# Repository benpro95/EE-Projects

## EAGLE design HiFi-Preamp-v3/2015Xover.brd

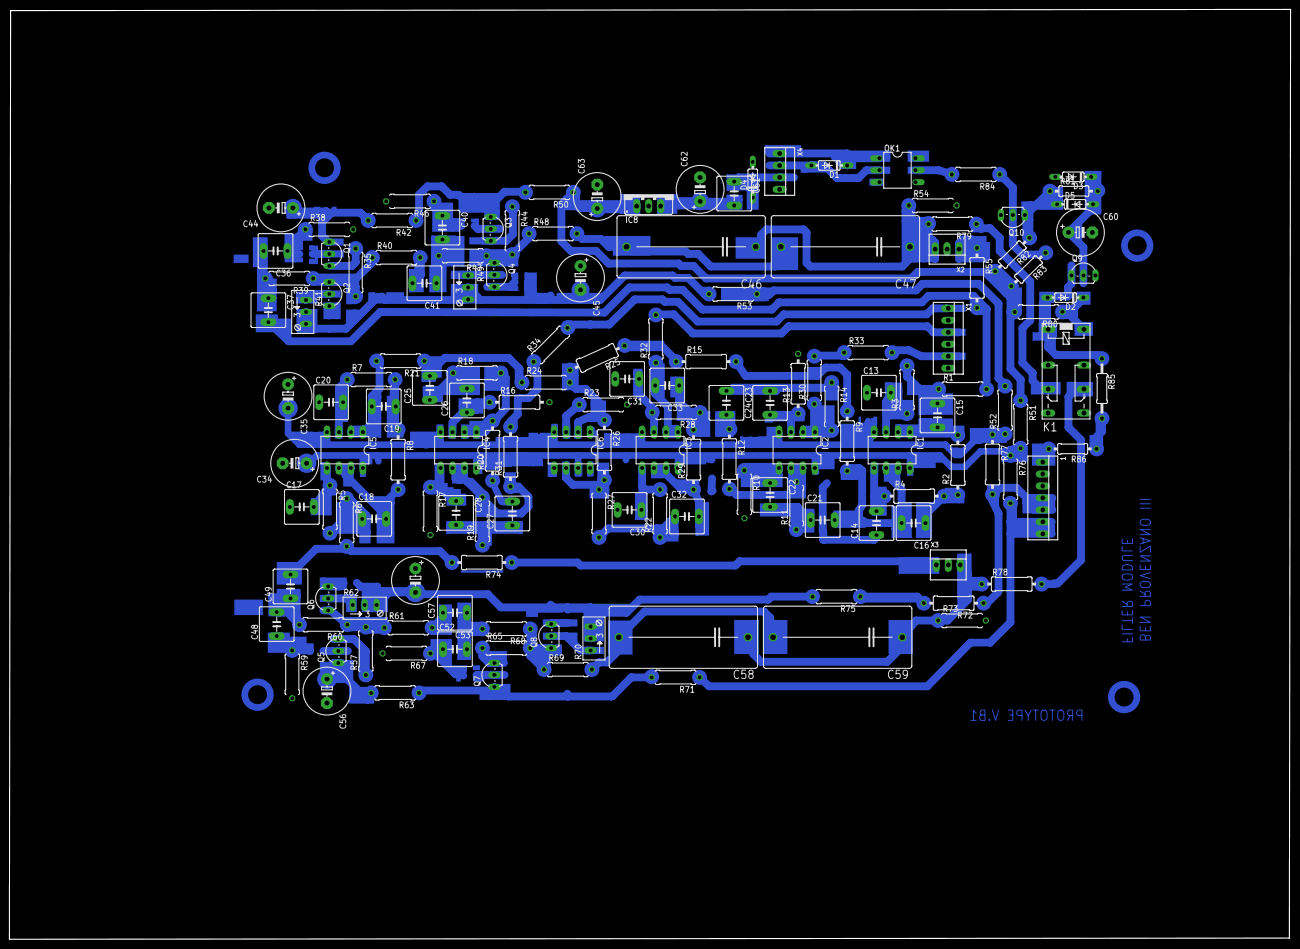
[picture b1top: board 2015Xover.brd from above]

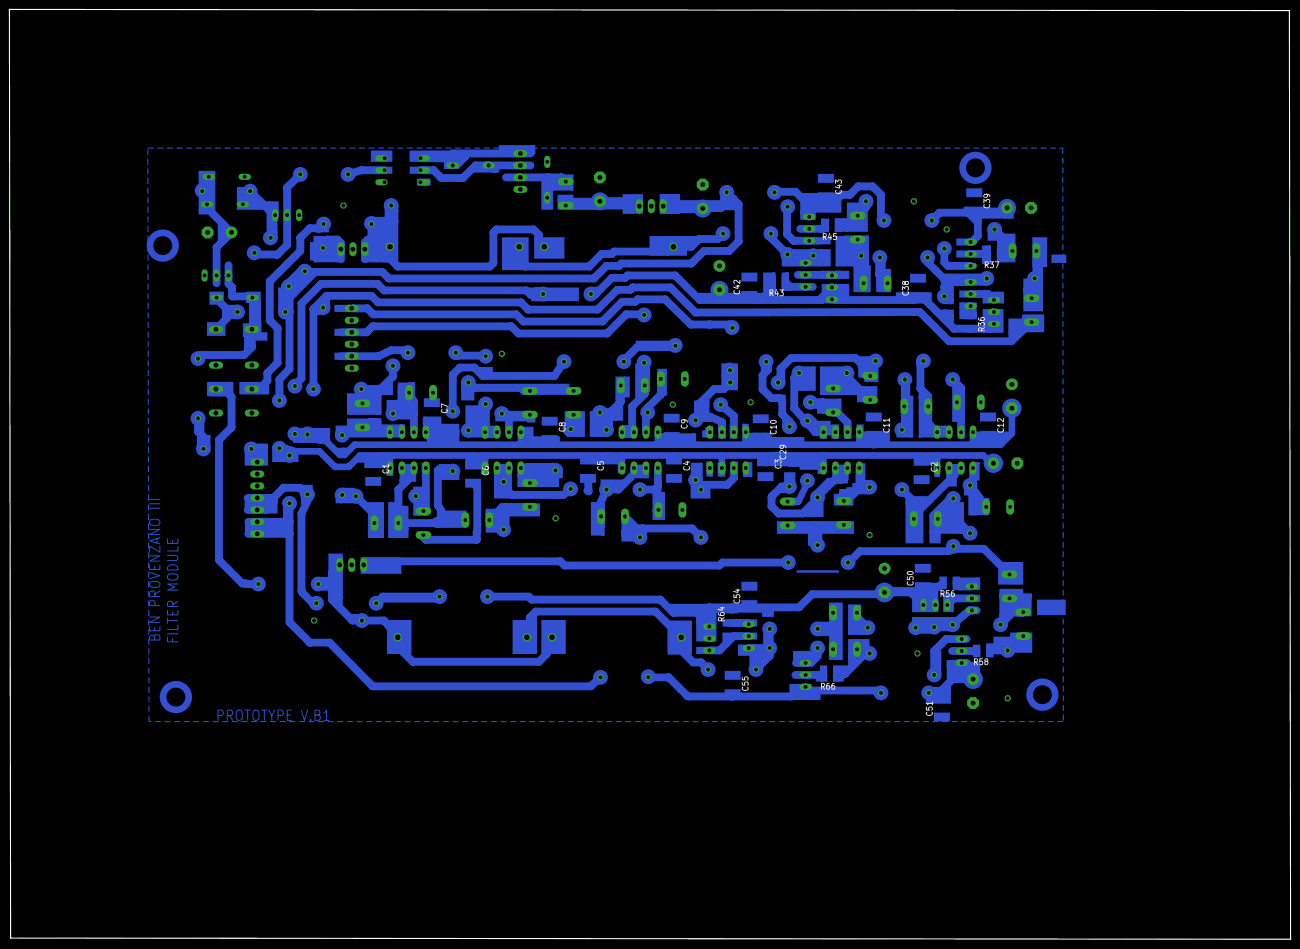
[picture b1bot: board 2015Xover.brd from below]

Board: 2 copper layers, 272.1 x 197.5 mm, 178 parts (29 on the bottom side), 109 nets.

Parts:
1: PWR; 22-23-2071
C1, C2, C3, C4, C5, C6, C7, C8, C9, C10, C11, C12, C29, C38, C39, C42, C43, C50, C51, C54, C55: .1; C4532
C13, C14, C17, C20, C36, C37, C40, C41, C48, C49, C52, C53: 33nF; C050-075X075
C15, C16, C18, C19: 2x33nF; C050-075X075
C21, C22, C23, C24, C25, C26, C27, C28, C30, C31: 100nF; C050-075X075
C32, C33: 2x100nF; C050-075X075
C34, C35, C44, C45, C56, C57, C60, C62: 100uF; E5-10,5
C46, C58: 3u3; C275-134X316
C47, C59: 1uF; C275-134X316
C61: .5APTC; C050-075X075
C63: 47uF; E5-10,5
D1, D5: 4148; DO35-7
D2: 4007; DO35-7
D3: 15v; DO35-7
D4: 15V; DO35-7
IC1, IC2, IC3, IC4, IC5: OPA2134P; DIL08
IC6: OPA134S; DIL08
IC8: 78XXS
K1: 351
OK1: 4N28; DIL06
Q1, Q3, Q5, Q7: K170; TO92-EBC
Q2, Q4, Q6, Q8: J112; TO92-EBC
Q9: 2106; TO92-EBC
Q10: BC546; TO92-EBC
R1: 15K; 0309/10
R2, R4, R8: 15k; 0309/12
R3, R5, R6, R7, R39, R47, R60, R68: 15k; 0309/10
R9, R12, R15, R20, R72, R78: 0; 0309/12
R10, R17: 50K; 0309/10
R11, R14, R18, R19, R22, R27, R28: 25K; 0309/10
R13, R16: 50K; 0309/12
R21, R42, R51, R52, R63, R79, R84: 0; 0309/10
R23: 1K; 0309/10
R24: 10K; 0309/10
R25, R26: 10K; 0309/12
R29: 25K; 0309/12
R30, R32, R40, R48, R61, R69: 118; 0309/10
R31: 118; 0309/12
R33, R34: NA; 0309/10
R35, R44, R50, R53, R57, R65, R71, R75: 5R1; 0309/10
R36, R37, R43, R45, R56, R58, R64, R66: 1K1; R1210
R38, R46, R59, R67: 30K; 0309/10
R41, R49, R62, R70: RJ9W
R54, R73: 100K; 0309/10
R55, R74: NA; 0309/12
R76: 0V+; 0309/10
R77: 0V-; 0309/12
R80: 220; 0309/10
R81: 2M2; 0207/10
R82, R83: 10K; 0207/10
R85: 0; 0207/12
R86: 0; 0207/10
X1: LPF; 22-23-2061
X2, X3: IO; 22-23-2031
X4: KK; 22-23-2041

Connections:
+15V: C1.1, C2.1, C3.1, C4.1, C5.1, C6.1, C29.1, C34.+, IC1.8, IC2.8, IC3.8, IC4.8, IC5.8, IC6.7, R51.2, R76.1
-15V: C7.2, C8.2, C9.2, C10.2, C11.2, C12.2, C29.2, C35.-, IC1.4, IC2.4, IC3.4, IC4.4, IC5.4, IC6.4, R52.1, R77.1
GND: 1.2, 1.3, C1.2, C2.2, C3.2, C4.2, C5.2, C6.2, C7.1, C8.1, C9.1, C10.1, C11.1, C12.1, C13.1, C14.1, C17.1, C20.1, C30.2, C31.2, C34.-, C35.+, C38.2, C39.1, C42.2, C43.1, C44.-, C45.+, C50.2, C51.1, C54.2, C55.1, C56.-, C57.+, C60.-, C62.-, C63.-, D3.A, D4.A, IC8.GND, K1.P1, K1.P2, K1.S1, K1.S2, OK1.4, Q9.E, Q10.E, R10.2, R13.2, R16.2, R17.2, R23.2, R38.2, R46.2, R54.2, R59.2, R67.2, R73.2, X1.2, X1.4, X1.6, X2.2, X3.2, X4.4
unnamed: C15.2, IC1.1, IC1.2, R2.2
unnamed: C23.1, C24.2, R14.1
unnamed: IC2.1, IC2.2, R14.2, R30.1
unnamed: IC2.6, IC2.7, R11.2, R12.2
unnamed: C33.2, IC3.1, IC3.2, R32.1
unnamed: C32.2, IC3.6, IC3.7, R29.1
unnamed: Q2.E, R36.1
unnamed: IC4.6, IC4.7, R19.2, R31.1
unnamed: C18.2, IC5.6, IC5.7, R8.2
unnamed: C19.2, IC5.1, IC5.2, R21.2
unnamed: C16.1, R2.1, R4.2
unnamed: C15.1, R1.1, R3.2
unnamed: C13.2, IC1.3, R3.1
unnamed: C14.2, IC1.5, R4.1
unnamed: C18.1, R5.2, R6.1
unnamed: C17.2, IC5.5, R5.1
unnamed: C20.2, IC5.3, R7.1
unnamed: C19.1, R7.2, R8.1
unnamed: C21.1, C22.2, R11.1
unnamed: C22.1, IC2.5, R10.1
unnamed: C16.2, C21.2, IC1.6, IC1.7, R9.2
unnamed: C24.1, IC2.3, R13.1
unnamed: C23.2, R12.1
unnamed: R9.1, R15.2
unnamed: C27.2, R20.1
unnamed: C27.1, C28.2, R19.1
unnamed: C28.1, IC4.5, R17.1
unnamed: C26.1, IC4.3, R16.1
unnamed: C25.1, C26.2, R18.1
unnamed: R30.2, R33.1
unnamed: R31.2, R34.1
unnamed: Q2.C, R35.2, R39.1, R40.1
unnamed: IC4.1, IC4.2, R18.2, R20.2
unnamed: Q1.E, R35.1
unnamed: C49.2, R6.2, R74.2
unnamed: C39.2, C44.+, Q1.C, R42.2
unnamed: IC6.2, R24.2, R25.2, R26.1
unnamed: IC6.6, R26.2, R27.1
unnamed: C25.2, R21.1, R24.1
unnamed: R15.1, R25.1
unnamed: Q1.B, R37.2
unnamed: C31.1, IC3.3, R28.2
unnamed: C30.1, IC3.5, R22.2
unnamed: C32.1, R22.1, R27.2
unnamed: C33.1, R28.1, R29.2
unnamed: Q2.B, R41.E
unnamed: C36.1, R37.1, R38.1
unnamed: R34.2, X1.1
unnamed: R32.2, X1.3
unnamed: R33.2, X1.5
unnamed: C36.2, C37.1, R39.2
unnamed: C37.2, R1.2, R55.2
unnamed: C41.2, R40.2
unnamed: IC6.3, R23.1
unnamed: C38.1, C42.1, C45.-, R36.2, R41.A, R41.S, R43.2, R49.A, R49.S, R53.2
unnamed: Q4.E, R43.1
unnamed: Q4.C, R44.2, R47.1, R48.1
unnamed: Q3.E, R44.1
unnamed: C43.2, Q3.C, R42.1, R50.2
unnamed: Q3.B, R45.2
unnamed: Q4.B, R49.E
unnamed: C40.1, R45.1, R46.1
unnamed: C40.2, C41.1, R47.2
unnamed: R52.2, R53.1
unnamed: OK1.5, R84.2
unnamed: C46.2, C47.2, R48.2
unnamed: C46.1, C47.1, R54.1, R79.2, X2.3
unnamed: R55.1, X2.1
unnamed: 1.6, 1.7, R71.1, R76.2
unnamed: Q6.E, R56.1
unnamed: Q6.C, R57.2, R60.1, R61.1
unnamed: Q5.E, R57.1
unnamed: C51.2, C56.+, Q5.C, R63.2
unnamed: Q5.B, R58.2
unnamed: Q6.B, R62.E
unnamed: C48.1, R58.1, R59.1
unnamed: C48.2, C49.1, R60.2
unnamed: C50.1, C54.1, C57.-, R56.2, R62.A, R62.S, R64.2, R70.A, R70.S, R75.2
unnamed: C53.2, R61.2
unnamed: Q8.E, R64.1
unnamed: Q8.C, R65.2, R68.1, R69.1
unnamed: Q7.E, R65.1
unnamed: C55.2, Q7.C, R63.1, R71.2
unnamed: Q7.B, R66.2
unnamed: Q8.B, R70.E
unnamed: C52.1, R66.1, R67.1
unnamed: C52.2, C53.1, R68.2
unnamed: D1.C, OK1.1, X4.1
unnamed: R72.2, R75.1
unnamed: C58.2, C59.2, R69.2
unnamed: C58.1, C59.1, R73.1, R78.1, X3.3
unnamed: R74.1, X3.1
unnamed: 1.4, 1.5, R72.1, R77.2
unnamed: D1.A, OK1.2, X4.2
unnamed: K1.O1, R79.1
unnamed: D2.C, K1.16, R80.1
unnamed: C60.+, D3.C, D5.A, Q9.B, R81.2
unnamed: K1.O2, R78.2
unnamed: D2.A, K1.1, Q9.C, R85.1
unnamed: C61.1, D4.C, X4.3
unnamed: C61.2, C62.+, IC8.OUT
unnamed: D5.C, Q10.C, R81.1, R82.1
unnamed: Q10.B, R83.1, R84.1
unnamed: C63.+, IC8.IN, R50.1, R51.1, R80.2, R82.2, R83.2
unnamed: R85.2, R86.1
unnamed: 1.1, R86.2

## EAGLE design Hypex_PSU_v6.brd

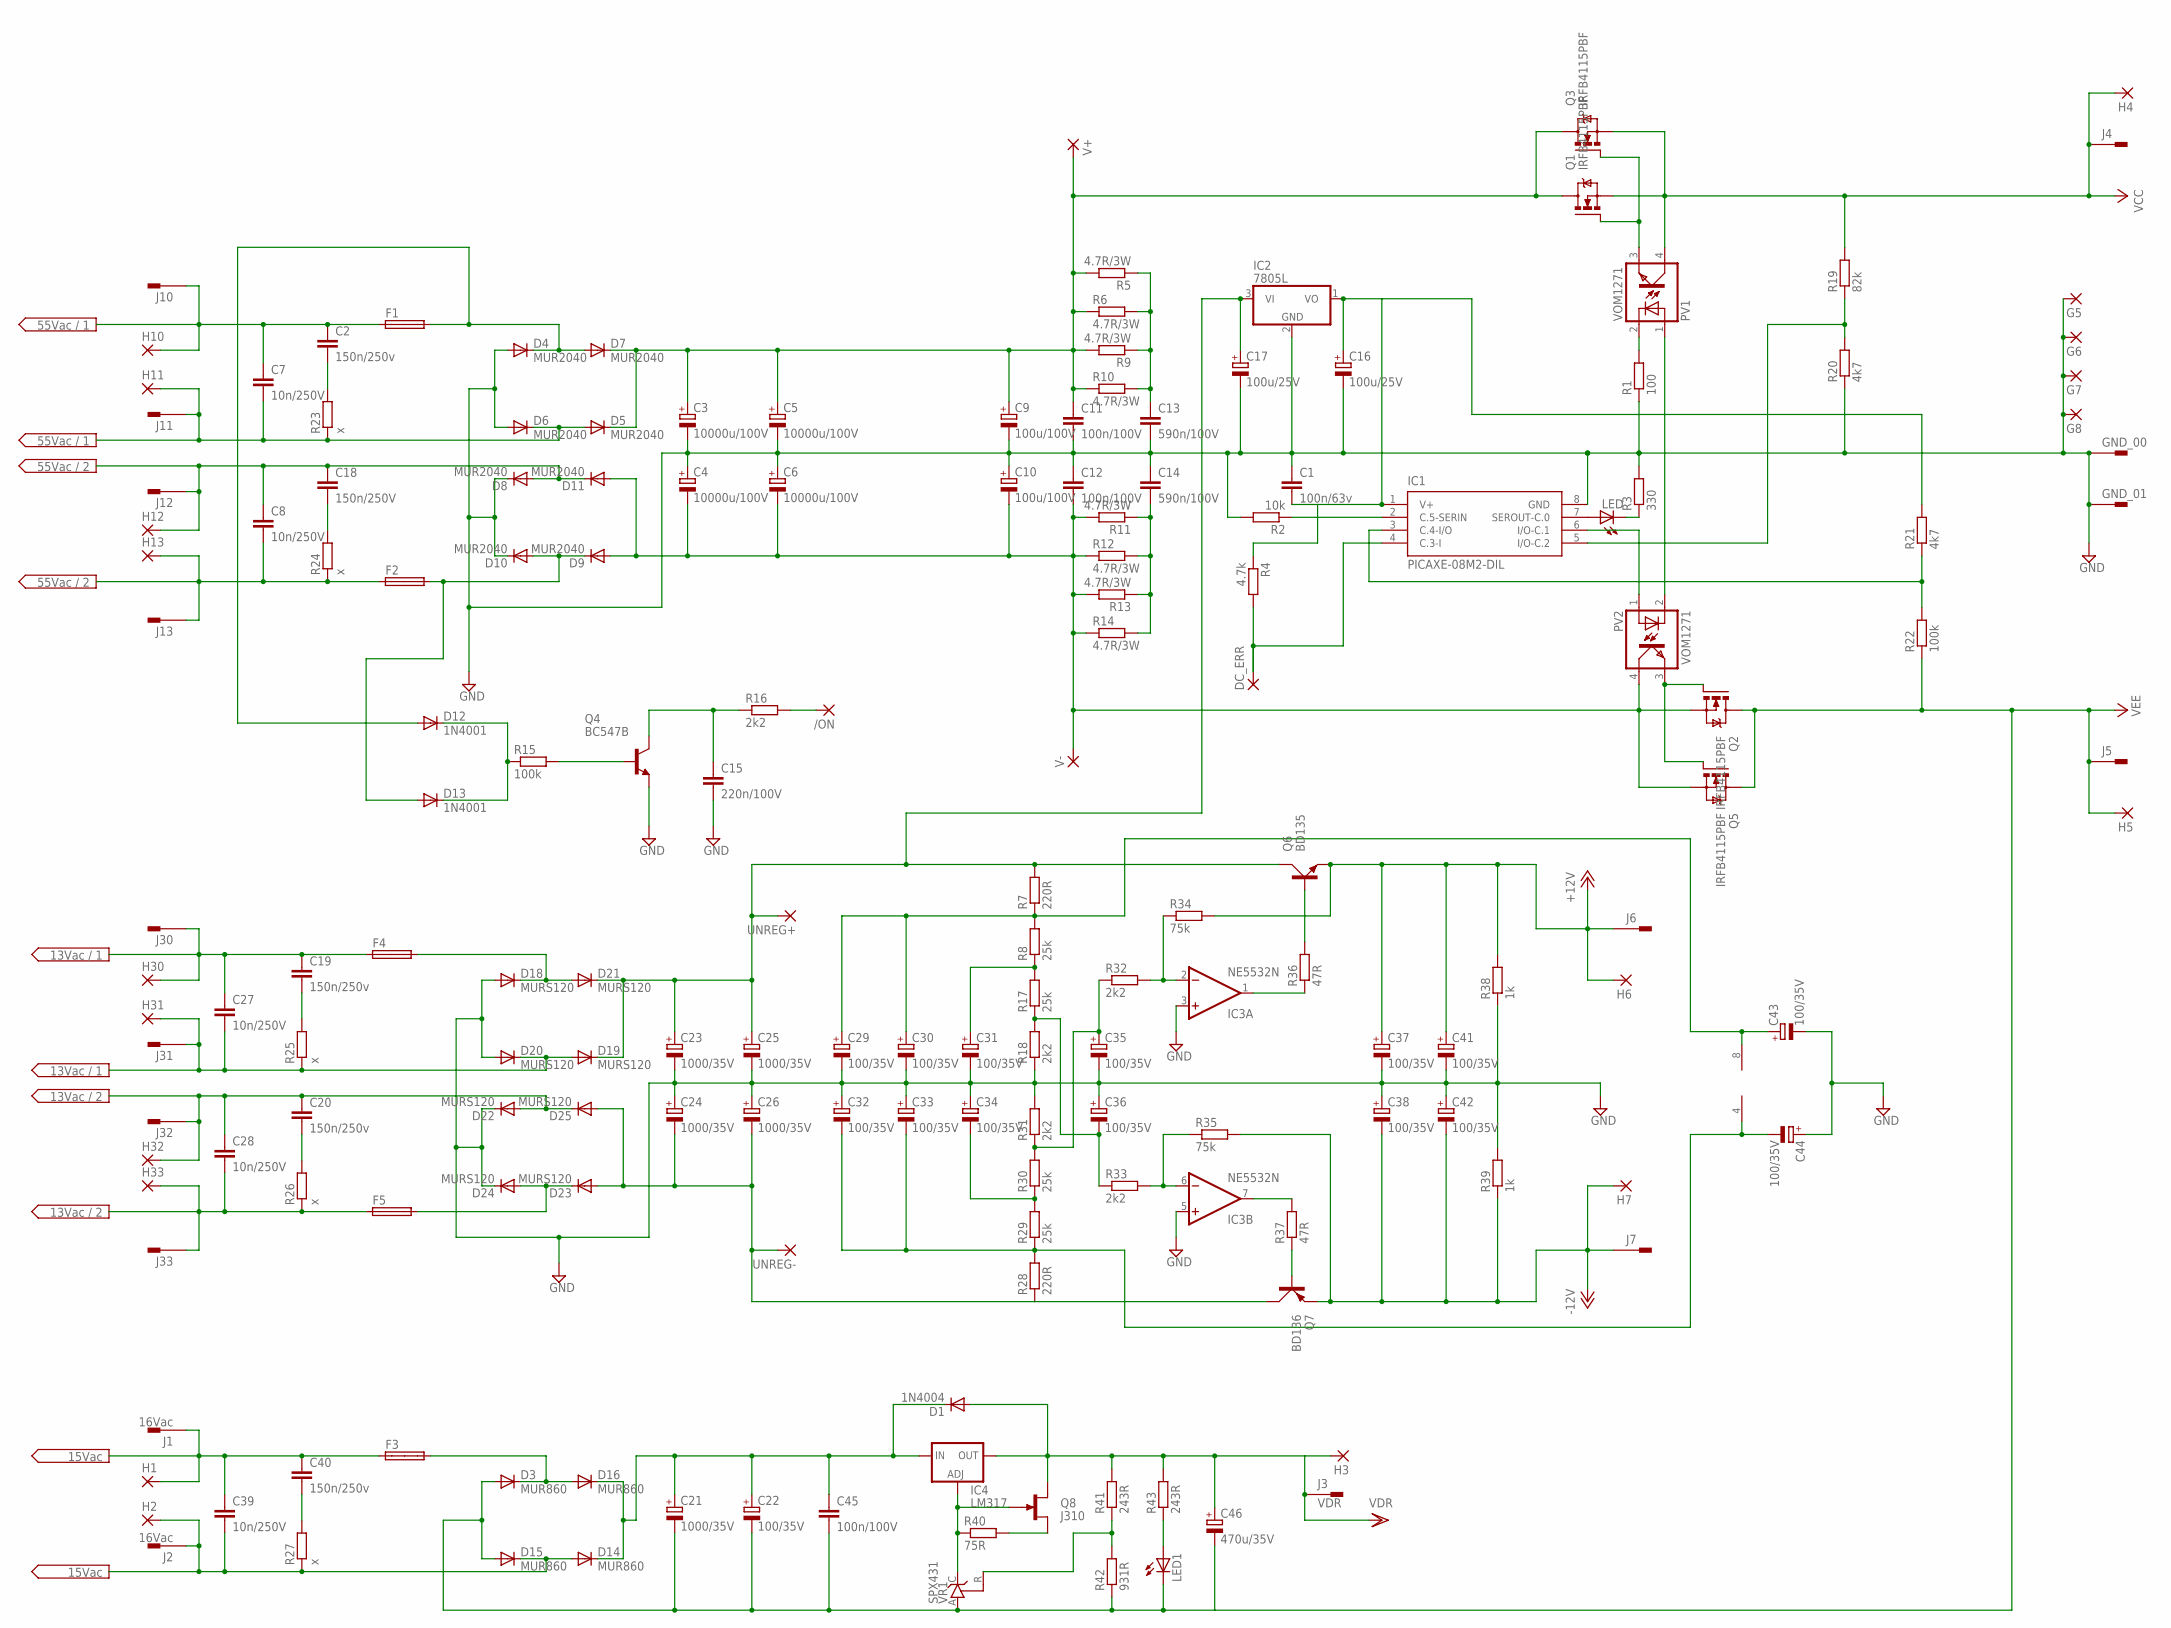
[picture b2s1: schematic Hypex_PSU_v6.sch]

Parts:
/ON: 2,54/0,8
C1: 100n/63v; C050-025X075
C2, C19, C20, C40: 150n/250v; C102-064X133
C3, C4, C5, C6: 10000u/100V; EB35D
C7, C8, C27, C28, C39: 10n/250V; C102-064X133
C9, C10: 100u/100V; E5-10,5
C11, C12, C45: 100n/100V; C102-064X133
C13, C14: 590n/100V; C102-064X133
C15: 220n/100V; C102-064X133
C16, C17: 100u/25V; E3,5-8
C18: 150n/250V; C102-064X133
C21, C23, C24, C25, C26: 1000/35V; E5-13
C22, C29, C30, C31, C32, C33, C34, C35, C36, C37, C38, C41, C42, C43, C44: 100/35V; E5-8,5
C46: 470u/35V; E5-8,5
D1: 1N4004; DO41-10
D3, D14, D15, D16: MUR860; TO220ACS
D4, D5, D6, D7, D8, D9, D10, D11: MUR2040; TO220ACS
D12, D13: 1N4001; DO41-10
D18, D19, D20, D21, D22, D23, D24, D25: MURS120; TO220ACS
DC_ERR: 2,54/0,8
F1, F2, F3, F4, F5: SHKOG
G5, G6, G7, G8: 3,17/1,3
GND_00, GND_01: PIN2F061.100; F061.100
H1, H2, H3, H6, H7, H10, H11, H12, H13, H30, H31, H32, H33: 3,81/1,4
H4, H5: 3,17/1,3
IC1: PICAXE-08M2-DIL; DIL8
IC2: 7805L; TO92
IC3: NE5532N; DIL08
IC4: LM317; 317TS
J1, J2: 16Vac; F061.100
J3: VDR; F061.100
J4, J5, J6, J7, J10, J11, J12, J13, J30, J31, J32, J33: PIN2F061.100; F061.100
LED, LED1: LED3MM
PV1, PV2: VOM1271; SMD4
Q1, Q2, Q3, Q5: IRFB4115PBF; TO220BV
Q4: BC547B; TO92
Q6: BD135; TO126AV
Q7: BD136; TO126AV
Q8: J310; TO92R
R1: 100; 0207/10
R2: 10k; 0207/10
R3: 330; 0207/10
R4: 4.7k; 0207/10
R5, R6, R9, R10, R11, R12, R13, R14: 4.7R/3W; 0617V
R7, R28: 220R; 0207/10
R8, R17, R29, R30: 25k; 0207/10
R15, R22: 100k; 0207/10
R16, R18, R31, R32, R33: 2k2; 0207/10
R19: 82k; 0207/10
R20, R21: 4k7; 0207/10
R23, R24: x; 0207/7
R25, R26, R27: x; 0207/10
R34, R35: 75k; 0207/10
R36, R37: 47R; 0207/10
R38, R39: 1k; 0207/10
R40: 75R; 0207/10
R41, R43: 243R; 0207/10
R42: 931R; 0207/10
UNREG+: 3,81/1,4
UNREG-: 3,81/1,4
V+: 3,81/1,4
V-: 3,81/1,4
VR1: SPX431; TO92-CLP

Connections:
+12V: C37.+, C41.+, H6.1, J6.A1, J6.A2, Q6.E, R34.2, R38.2
-12V: C38.-, C42.-, H7.1, J7.A1, J7.A2, Q7.E, R35.2, R39.1
GND: C1.1, C3.-, C4.+, C5.-, C6.+, C9.-, C10.+, C11.2, C12.1, C13.2, C14.1, C15.2, C16.-, C17.-, C23.-, C24.+, C25.-, C26.+, C29.-, C30.-, C31.-, C32.+, C33.+, C34.+, C35.-, C36.+, C37.-, C38.+, C41.-, C42.+, C43.-, C44.+, D4.A, D6.A, D8.C, D10.C, D18.A, D20.A, D22.C, D24.C, G5.1, G6.1, G7.1, G8.1, GND_00.A1, GND_00.A2, GND_01.A1, GND_01.A2, IC1.8 (GND), IC2.2 (GND), IC3.3 (+IN), IC3.5 (+IN), Q4.1 (E), R1.1, R2.2, R3.2, R18.1, R20.1, R31.2, R38.1, R39.2
unnamed: C1.2, C16.+, IC1.1 (V+), IC2.1 (VO), R4.1, R21.2
unnamed: DC_ERR.1, IC1.4 (C.3-I), R4.2
unnamed: PV1.3 (EMIT), Q1.G, Q3.G
unnamed: PV1.1 (A), PV2.2 (C)
unnamed: PV2.3 (EMIT), Q2.G, Q5.G
unnamed: PV1.2 (C), R1.2
unnamed: IC1.6 (I/O-C.1), PV2.1 (A)
unnamed: C27.2, D19.A, D20.C, H31.1, J31.A1, J31.A2, R25.1
unnamed: C2.1, C7.1, F1.1A, H10.1, J10.A1, J10.A2
unnamed: IC1.5 (I/O-C.2), R19.1, R20.2
unnamed: C13.1, R5.1, R6.2, R9.1, R10.2
unnamed: C20.1, C28.1, D22.A, D25.C, H32.1, J32.A1, J32.A2
unnamed: C7.2, D5.A, D6.C, H11.1, J11.A1, J11.A2, R23.1
unnamed: C14.2, R11.1, R12.2, R13.1, R14.2
unnamed: D9.C, D10.A, D13.A, F2.2A
unnamed: C8.1, C18.1, D8.A, D11.C, H12.1, J12.A1, J12.A2
unnamed: /ON.1, R16.2
unnamed: C2.2, R23.2
unnamed: D4.C, D7.A, D12.A, F1.2A
unnamed: C8.2, F2.1A, H13.1, J13.A1, J13.A2, R24.1
unnamed: IC1.2 (C.5-SERIN), R2.1
unnamed: IC1.7 (SEROUT-C.0), LED.A
unnamed: D12.C, D13.C, R15.1
unnamed: Q4.2 (B), R15.2
unnamed: C15.1, Q4.3 (C), R16.1
unnamed: LED.K (C), R3.1
unnamed: C18.2, R24.2
unnamed: D23.C, D24.A, F5.2A
unnamed: IC1.3 (C.4-I/O), R21.1, R22.2
unnamed: D18.C, D21.A, F4.2A
unnamed: C19.2, R25.2
unnamed: C20.2, R26.2
unnamed: C40.2, R27.2
unnamed: C36.-, R17.1, R18.2, R33.1
unnamed: C35.+, R30.2, R31.1, R32.1
unnamed: C39.2, D14.A, D15.C, H2.1, J2.A1, J2.A2, R27.1
unnamed: D3.C, D16.A, F3.2A
unnamed: C39.1, C40.1, F3.1A, H1.1, J1.A1, J1.A2
unnamed: C19.1, C27.1, F4.1A, H30.1, J30.A1, J30.A2
unnamed: C31.+, R8.1, R17.2
unnamed: C34.-, R29.2, R30.1
unnamed: C29.+, C30.+, C43.+, IC3.8 (V+), R7.1, R8.2
unnamed: C32.-, C33.-, C44.-, IC3.4 (V-), R28.2, R29.1
unnamed: C21.+, C22.+, C45.1, D1.C, D14.C, D16.C, IC4.3 (IN)
unnamed: IC3.1 (OUT), R36.1
unnamed: IC3.2 (-IN), R32.2, R34.1
unnamed: IC3.6 (-IN), R33.2, R35.1
unnamed: Q6.B, R36.2
unnamed: IC3.7 (OUT), R37.2
unnamed: Q7.B, R37.1
unnamed: C28.2, F5.1A, H33.1, J33.A1, J33.A2, R26.1
unnamed: IC4.1 (ADJ), Q8.G, R40.1, VR1.C
unnamed: Q8.S, R40.2
unnamed: R41.1, R42.2, VR1.R
unnamed: LED1.A, R43.1
VCC: H4.1, J4.A1, J4.A2, PV1.4 (COL), Q1.S, Q3.S, R19.2
VCC_IN: C3.+, C5.+, C9.+, C11.1, D5.C, D7.C, Q1.D, Q3.D, R5.2, R6.1, R9.2, R10.1, V+.1
VCC_IN1: C17.+, C23.+, C25.+, D19.C, D21.C, IC2.3 (VI), Q6.C, R7.2, UNREG+.1
VDD: C46.+, D1.A, H3.1, IC4.2 (OUT), J3.A1, J3.A2, Q8.D, R41.2, R43.2
VEE: C21.-, C22.-, C45.2, C46.-, D3.A, D15.A, H5.1, J5.A1, J5.A2, LED1.K (C), Q2.D, Q5.D, R22.1, R42.1, VR1.A
VEE_IN: C4.-, C6.-, C10.-, C12.2, D9.A, D11.A, PV2.4 (COL), Q2.S, Q5.S, R11.2, R12.1, R13.2, R14.1, V-.1
VEE_IN1: C24.-, C26.-, D23.A, D25.A, Q7.C, R28.1, UNREG-.1

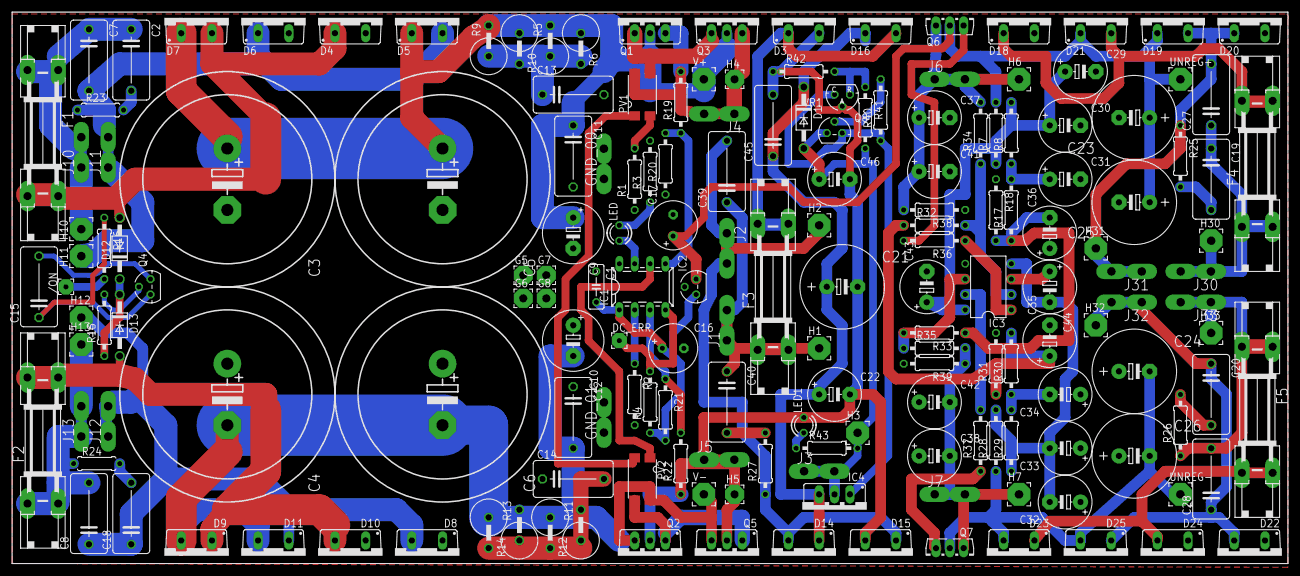
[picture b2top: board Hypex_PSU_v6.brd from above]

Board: 2 copper layers, 210.8 x 91.1 mm, 176 parts (0 on the bottom side), 65 nets.

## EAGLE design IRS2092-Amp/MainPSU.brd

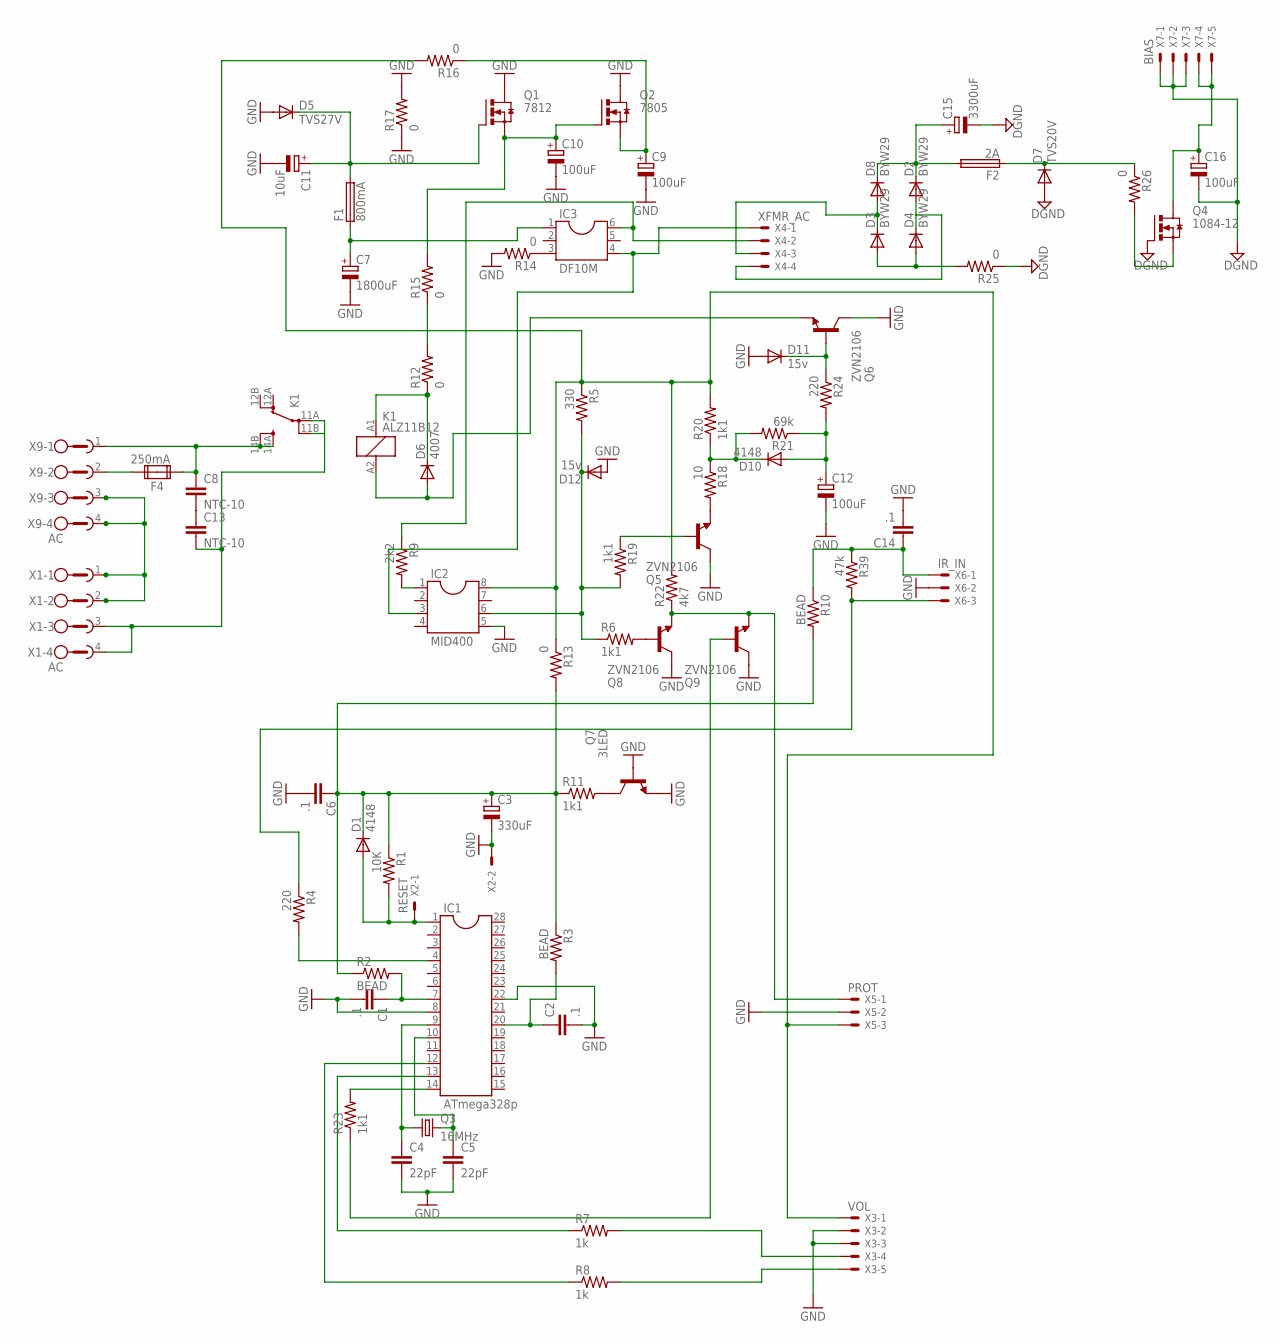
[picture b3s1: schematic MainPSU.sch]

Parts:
C1, C2, C6, C14: .1; C1210K
C3: 330uF; E3,5-10
C4, C5: 22pF; C1210K
C7: 1800uF; E7,5-16
C8, C13: NTC-10; C102-054X133
C9, C10, C12, C16: 100uF; E3,5-10
C11: 10uF; E3,5-10
C15: 3300uF; E7,5-16
D1: 4148; DO35-7
D2, D3, D4, D8: BYW29; DO220S
D5: TVS27V; SOD57-10
D6: 4007; DO41-10
D7: TVS20V; SOD57-10
D10: 4148; DO35-10
D11, D12: 15v; DO35-7
F1: 800mA; 19560
F2: 2A; 19560
F4: 250mA; FUSE1
IC1: ATmega328p; DIL28-3
IC2: MID400; DIL08
IC3: DF10M; DIL06
K1: ALZ11B12; RT-C/O16A5
Q1: 7812; TO220BH
Q2: 7805; TO220BH
Q3: 16MHz; HC49/S
Q4: 1084-12; TO220BH
Q5, Q6, Q8, Q9: ZVN2106; TO92-EBC
Q7: 3LED; TO92-EBC
R1: 10K; 0309/10
R2, R10: BEAD; 0309/10
R3: BEAD; 0309/12
R4: 220; 0309/12
R5: 330; 0309/10
R6, R19: 1k1; 0309/12
R7, R8: 1k; R1210
R9: 2k2; 0309/12
R11, R20: 1k1; 0309/10
R12, R14: 0; 0309/10
R13, R15, R16, R17, R25, R26: 0; 0309/12
R18: 10; 0207/5V
R21: 69k; 0309/10
R22: 4k7; 0309/10
R23: 1k1; R1210
R24: 220; 0309/10
R39: 47k; 0309/10
X1, X9: AC; GMSTBA4
X2: RESET; 22-23-2021
X3: VOL; 22-23-2051
X4: XFMR_AC; 5566-4
X5: PROT; 22-23-2031
X6: IR_IN; 22-23-2031
X7: BIAS; 22-23-2051

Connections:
DGND: C15.-, C16.-, D7.A, Q4.G, R25.1, X7.1, X7.2, X7.3
GND: C1.2, C2.2, C3.-, C4.2, C5.2, C6.2, C7.-, C9.-, C10.-, C11.-, C12.-, C14.2, D5.A, D11.A, D12.A, IC1.8, IC1.22, IC2.5, Q1.D, Q2.D, Q5.C, Q6.C, Q7.B, Q7.E, Q8.C, Q9.C, R14.2, R17.1, R17.2, X2.2, X3.2, X3.3, X5.2, X6.2
unnamed: Q8.B, R6.2
unnamed: D1.A, IC1.1, R1.2, X2.1
unnamed: IC1.4, R4.2
unnamed: C2.1, IC1.20, R3.2
unnamed: R4.1, R39.2, X6.3
unnamed: IC1.13, R7.1
unnamed: IC1.12, R8.1
unnamed: C11.+, D5.C, F1.2, Q1.G
unnamed: C8.2, C13.1
unnamed: D6.C, K1.A1 (1), R12.1
unnamed: IC3.6, R9.1, X4.2
unnamed: C4.1, IC1.9, Q3.1
unnamed: C5.1, IC1.10, Q3.2
unnamed: X1.1, X1.2, X9.3, X9.4
unnamed: D12.C, IC2.6, R5.2, R6.1, R19.2
unnamed: IC2.1, R9.2
unnamed: Q8.E, Q9.E, R22.1, X5.1
unnamed: IC3.3, R14.1
unnamed: C14.1, R10.1, R39.1, X6.1
unnamed: F4.2A, X9.2
unnamed: Q7.C, R11.2
unnamed: C8.1, F4.1A, K1.14A (SA), K1.14B (SB), X9.1
unnamed: C13.2, K1.11A (PA), K1.11B (PB), X1.3, X1.4
unnamed: C9.+, Q2.S, R16.1
unnamed: C10.+, Q1.S, Q2.G, R15.2
unnamed: R12.2, R15.1
unnamed: C7.+, F1.1, IC3.1
unnamed: C3.+, C6.1, D1.C, R1.1, R2.1, R3.1, R10.2, R11.1, R13.2
unnamed: D3.C, D8.A, X4.3
unnamed: D2.A, D4.C, X4.4
unnamed: C1.1, IC1.7, R2.2
unnamed: IC2.8, R5.1, R13.1, R16.2, R20.2, R22.2, X3.1, X5.3
unnamed: IC2.3, IC3.4, X4.1
unnamed: Q5.B, R19.1
unnamed: D10.C, R18.1, R20.1, R21.2
unnamed: C12.+, D10.A, R21.1, R24.2
unnamed: IC1.14, R23.2
unnamed: D6.A, K1.A2 (2), Q6.E
unnamed: D11.C, Q6.B, R24.1
unnamed: Q9.B, R23.1
unnamed: R8.2, X3.5
unnamed: R7.2, X3.4
unnamed: D3.A, D4.A, R25.2
unnamed: C15.+, D2.C, D8.C, F2.2
unnamed: D7.C, F2.1, R26.1
unnamed: Q4.S, R26.2
unnamed: Q5.E, R18.2
unnamed: C16.+, Q4.D, X7.4, X7.5

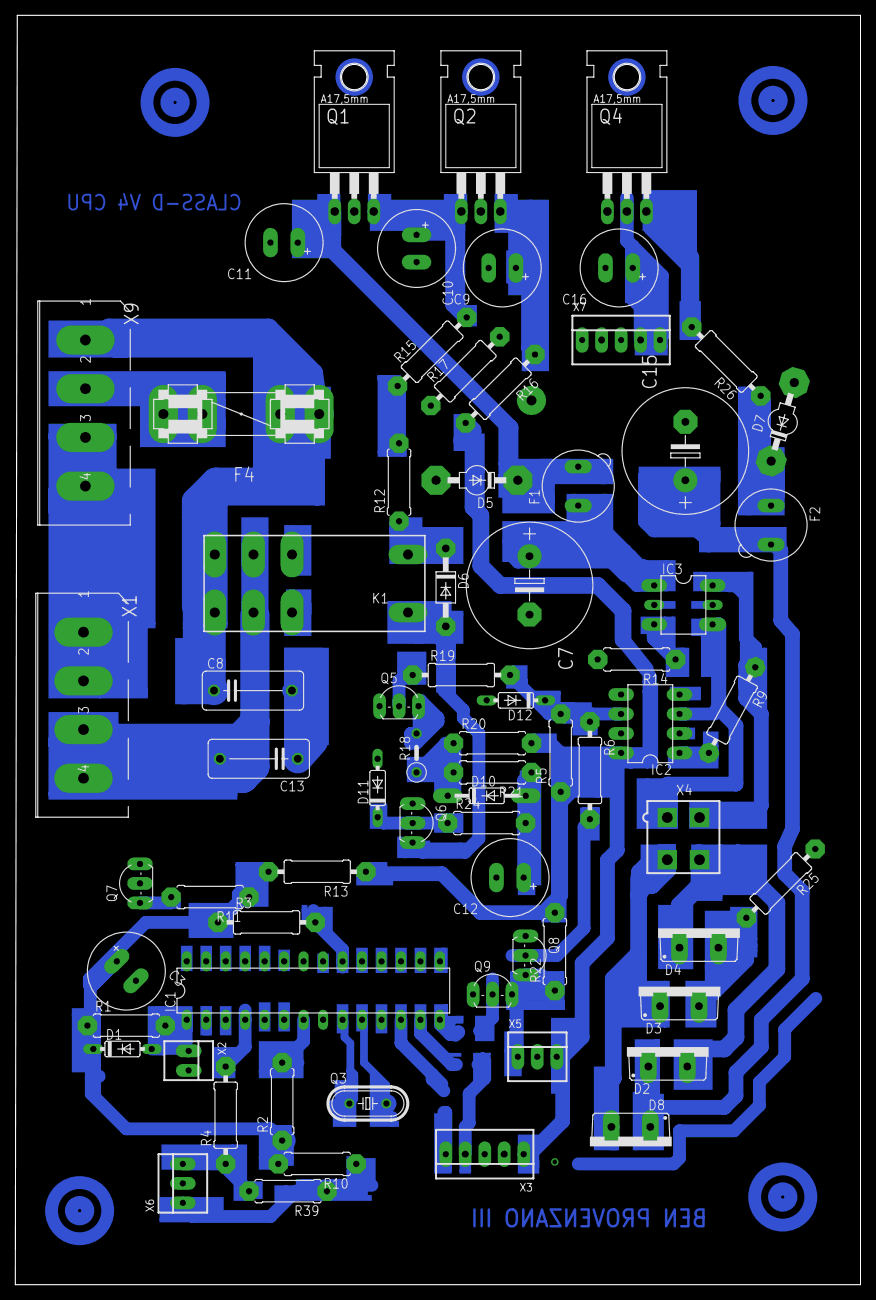
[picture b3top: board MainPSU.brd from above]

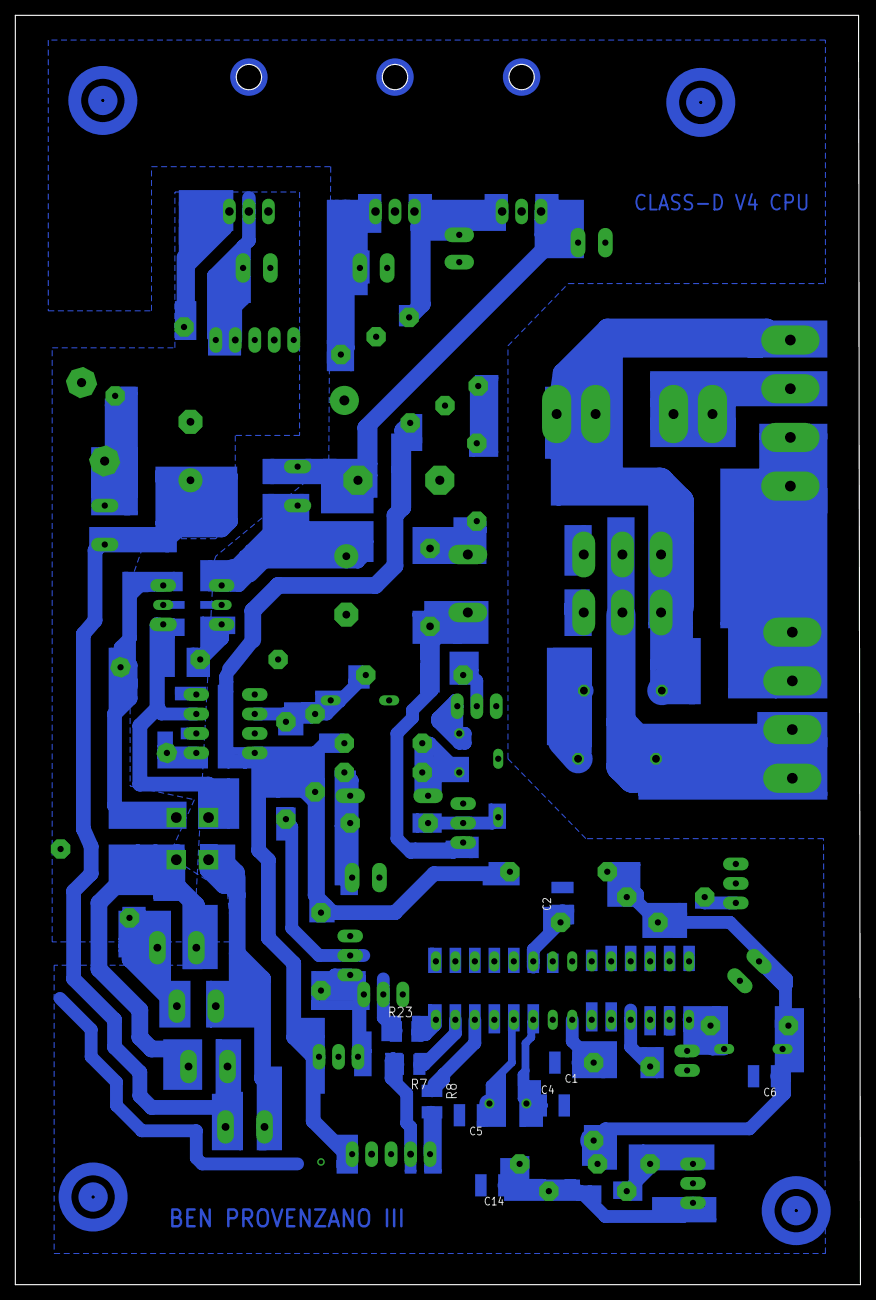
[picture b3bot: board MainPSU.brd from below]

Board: 2 copper layers, 110.2 x 165.5 mm, 78 parts (9 on the bottom side), 50 nets.

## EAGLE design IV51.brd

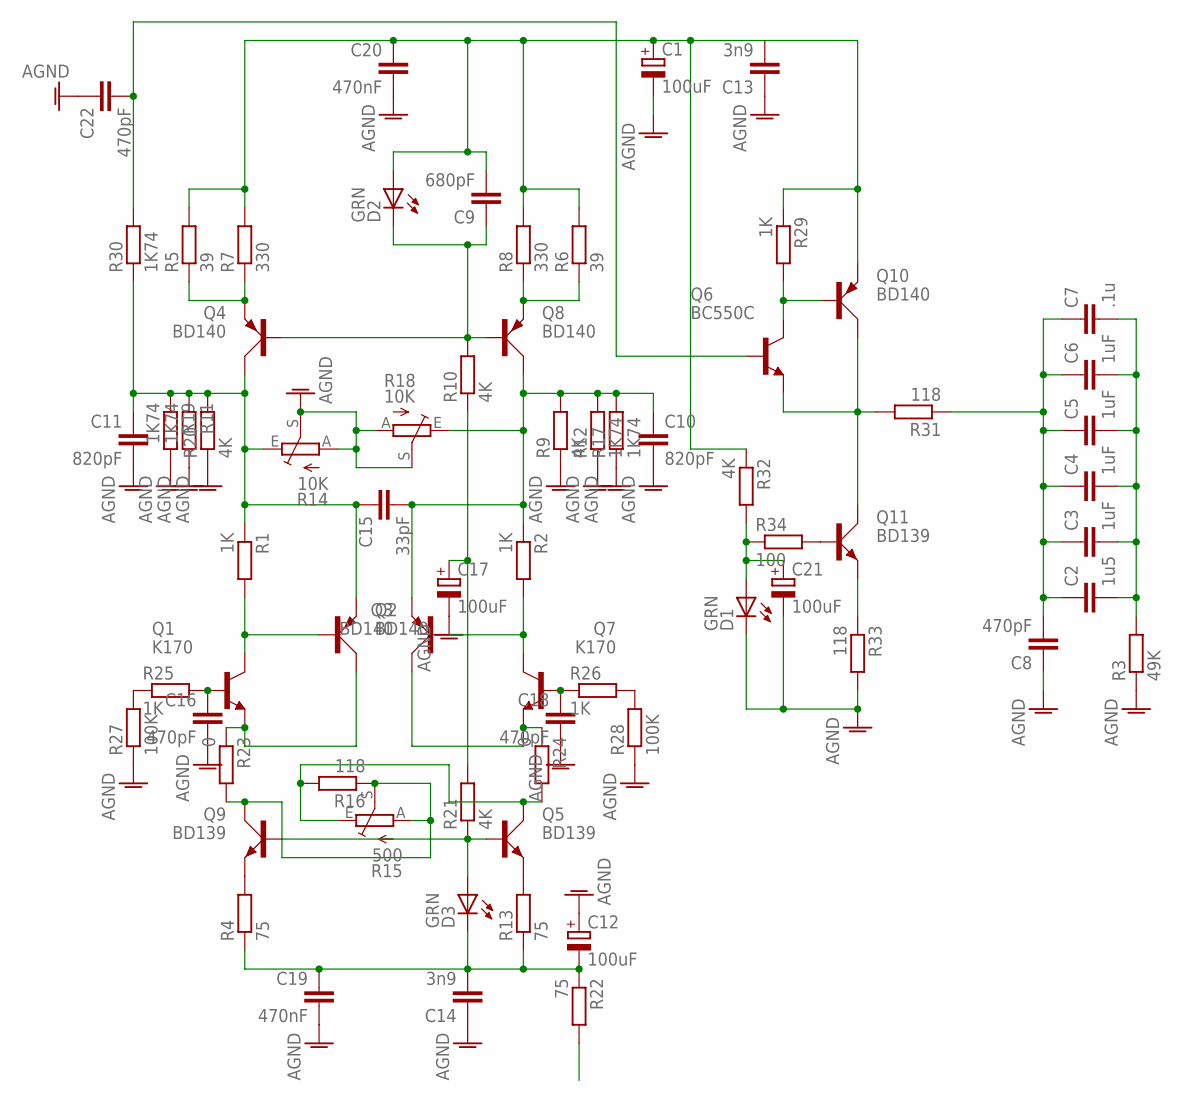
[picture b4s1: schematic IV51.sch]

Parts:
C1, C12: 100uF; E5-10,5
C2: 1u5; C275-134X316
C3, C4, C5, C6: 1uF; C275-134X316
C7: .1u; C050-075X075
C8, C16, C18: 470pF; C102-043X133
C9: 680pF; C050-045X075
C10, C11: 820pF; C075-032X103
C13, C14: 3n9; C1210
C15: 33pF; C1210
C17, C21: 100uF; E3,5-8
C19, C20: 470nF; C102-043X133
C22: 470pF; C075-042X103
D1, D2, D3: GRN; SFH482
Q1, Q7: K170; TO92-EBC
Q2, Q3, Q4, Q8, Q10: BD140; TO126AV
Q5, Q9, Q11: BD139; TO126AV
Q6: BC550C; TO92-EBC
R1, R2, R25, R26: 1K; 0309/12
R3: 49K; 0309/12
R4, R13, R22: 75; 0309/12
R5, R6: 39; 0309/12
R7, R8: 330; 0309/12
R9, R10, R20, R21, R32: 4K; 0309/12
R11, R12, R17, R19, R30: 1K74; 0309/12
R14, R18: 10K; RJ9W
R15: 500; PT-SPIN
R16, R31, R33: 118; 0309/12
R23, R24: 0; 0309/10
R27, R28: 100K; 0309/12
R29: 1K; R1210
R34: 100; R1210

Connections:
AGND: C1.-, C8.1, C10.2, C11.2, C12.+, C13.1, C14.1, C16.2, C17.-, C18.2, C19.2, C20.2, C21.-, C22.1, D1.K (C), R3.1, R9.1, R11.2, R12.1, R14.A, R14.S, R17.1, R18.A, R18.S, R19.2, R20.1, R27.1, R28.1, R33.2
unnamed: Q9.E, R4.2
unnamed: Q4.E, R5.1, R7.1
unnamed: C2.1, C3.1, C4.1, C5.1, C6.1, C7.1, C8.2, R31.1
unnamed: Q1.C, Q2.B, R1.2
unnamed: C1.+, C9.2, C13.2, C20.1, D2.A, Q10.E, R5.2, R6.2, R7.2, R8.2, R29.1, R32.1
unnamed: Q3.B, Q7.C, R2.2
unnamed: Q5.E, R13.2
unnamed: C17.+, R10.1, R21.2
unnamed: C16.1, Q1.B, R25.2
unnamed: Q3.C, Q7.E, R24.1
unnamed: Q8.E, R6.1, R8.1
unnamed: C10.1, C15.2, Q3.E, Q8.C, R2.1, R9.2, R12.2, R17.2, R18.E
unnamed: C18.1, Q7.B, R26.1
unnamed: C9.1, D2.K (C), Q4.B, Q8.B, R10.2
unnamed: C22.2, Q6.B, R30.2
unnamed: Q1.E, Q2.C, R23.1
unnamed: Q5.C, R15.E, R16.2, R24.2
unnamed: Q9.C, R15.A, R15.S, R16.1, R23.2
unnamed: R25.1, R27.2
unnamed: C12.-, C14.2, C19.1, D3.K (C), R4.1, R13.1, R22.1
unnamed: D3.A, Q5.B, Q9.B, R21.1
unnamed: R26.2, R28.2
unnamed: Q6.C, Q10.B, R29.2
unnamed: Q6.E, Q10.C, Q11.C, R31.2
unnamed: Q11.B, R34.2
unnamed: C11.1, C15.1, Q2.E, Q4.C, R1.1, R11.1, R14.E, R19.1, R20.2, R30.1
unnamed: C21.+, D1.A, R32.2, R34.1
unnamed: Q11.E, R33.1
OUT: C2.2, C3.2, C4.2, C5.2, C6.2, C7.2, R3.2
